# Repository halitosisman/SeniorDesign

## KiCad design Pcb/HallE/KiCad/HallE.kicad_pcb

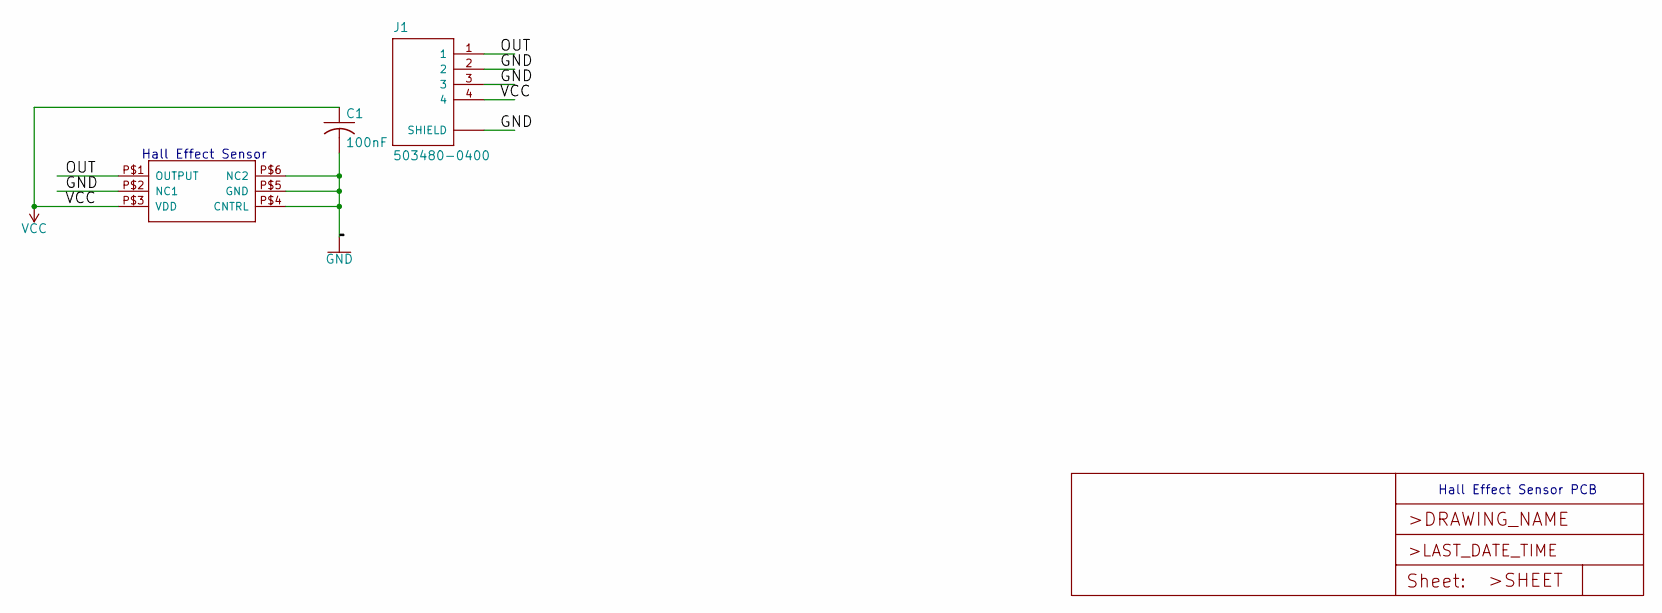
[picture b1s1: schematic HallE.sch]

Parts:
C1: 100nF; C0805
J1: 503480-0400; MOLEX_503480-0400
U$1: AH8503; UDFN-6

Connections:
/OUT: J1.1, U$1.P$1 (OUTPUT)
GND: C1.2, J1.2, J1.3, J1.S1 (SHIELD), J1.S2 (SHIELD), U$1.P$2 (NC1), U$1.P$4 (CNTRL), U$1.P$5 (GND), U$1.P$6 (NC2)
VCC: C1.1, J1.4, U$1.P$3 (VDD)

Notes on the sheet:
Hall Effect Sensor PCB
Hall Effect Sensor

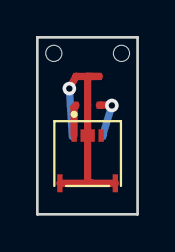
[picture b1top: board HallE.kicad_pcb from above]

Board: 2 copper layers, 5.6 x 9.8 mm, 5 parts (0 on the bottom side), 3 nets.

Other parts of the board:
@HOLE0, @HOLE1: (no value)

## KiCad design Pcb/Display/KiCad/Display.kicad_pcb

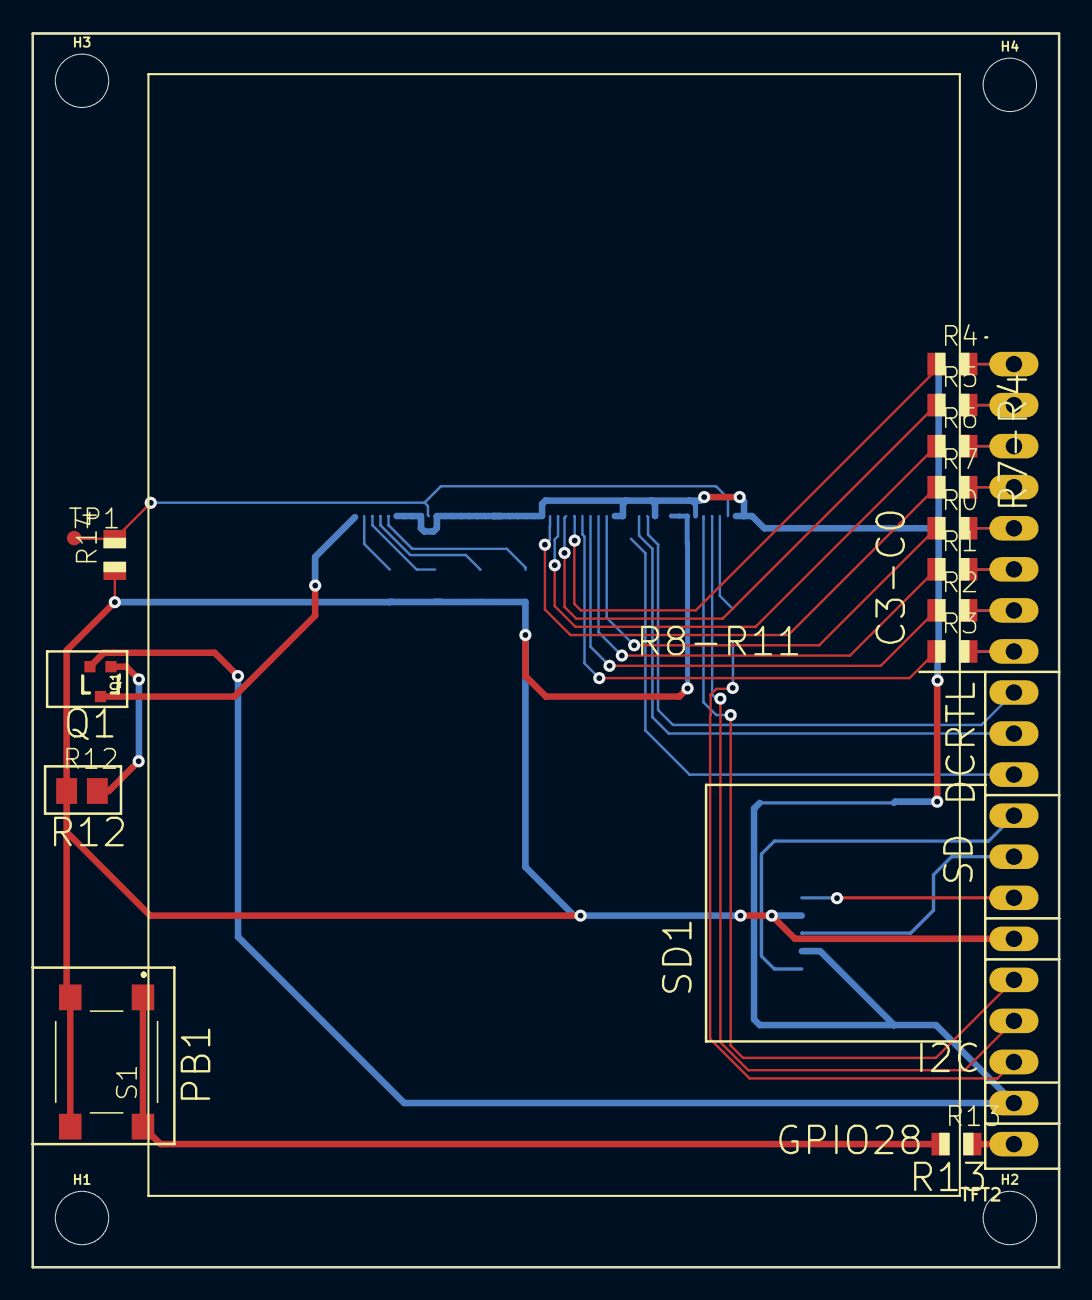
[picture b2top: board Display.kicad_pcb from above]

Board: 2 copper layers, 63.5 x 76.4 mm, 34 parts (0 on the bottom side), 37 nets.

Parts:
C0, C1, C2, C3, C4, C5, C6, C7: 10pF; C0805
H1, H2, H3, H4: STAND-OFF
J2: 47219-2001; MOLEX_47219-2001
JP4: Main PCB Header; 1X20
Q1: 310mA/60V/1.6Ω; SOT323
R0, R1, R2, R3, R4, R5, R6, R7, R8, R9, R10, R11, R14: 10; R0805
R12: 2.2k; M0805
R13: 100; R0805
R15: 1k; R0805
S1: B3FS-1000; B3FS1000
TFT2: DISP_LCD_CTP28_DATASHEET; TFT_CTP28
TP1: TPTP09R; TP09R

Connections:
/DB0: C0.1, JP4.16, R0.2
/DB1: C1.1, JP4.15, R1.2
/DB2: C2.1, JP4.14, R2.2
/DB3: C3.1, JP4.13, R3.2
/DB4: C4.1, JP4.20, R4.2
/DB5: C5.1, JP4.19, R5.2
/DB6: C6.1, JP4.18, R6.2
/DB7: C7.1, JP4.17, R7.2
/DCX: JP4.12, TFT2.37
/GPIO28: JP4.1, R13.2
/I2C_INT: JP4.3, R15.1
/I2C_SCL: JP4.5, TFT2.44
/I2C_SDA: JP4.4, TFT2.45
/R8: R8.2, TFT2.5
/R9: R9.2, TFT2.4
/R10: R10.2, TFT2.3
/R11: R11.2, TFT2.2
/R12: Q1.3, TFT2.1
/R13: R13.1, S1.1, S1.2
/RST: R14.2, TFT2.10, TFT2.47, TP1.TP
/SD_CLK: J2.5, JP4.8
/SD_CMD: J2.3, JP4.7
/SD_DAT0: J2.7, JP4.9
GND: C0.2, C1.2, C2.2, C3.2, C4.2, C5.2, C6.2, C7.2, J2.6, J2.G1, J2.G2, J2.G3, J2.G4, JP4.2, Q1.2, TFT2.6, TFT2.7, TFT2.8, TFT2.9, TFT2.11, TFT2.12, TFT2.13, TFT2.14, TFT2.15, TFT2.16, TFT2.17, TFT2.18, TFT2.19, TFT2.20, TFT2.21, TFT2.22, TFT2.23, TFT2.24, TFT2.33, TFT2.34, TFT2.38, TFT2.43, TFT2.48, TFT2.49, TFT2.50
unnamed: JP4.10, TFT2.36
unnamed: JP4.11, TFT2.35
unnamed: Q1.1, R12.2
unnamed: R0.1, TFT2.32
unnamed: R1.1, TFT2.31
unnamed: R2.1, TFT2.30
unnamed: R3.1, TFT2.29
unnamed: R4.1, TFT2.28
unnamed: R5.1, TFT2.27
unnamed: R6.1, TFT2.26
unnamed: R7.1, TFT2.25
unnamed: R15.2, TFT2.46
VCC: J2.4, JP4.6, R8.1, R9.1, R10.1, R11.1, R12.1, R14.1, S1.3, S1.4, TFT2.40, TFT2.41, TFT2.42

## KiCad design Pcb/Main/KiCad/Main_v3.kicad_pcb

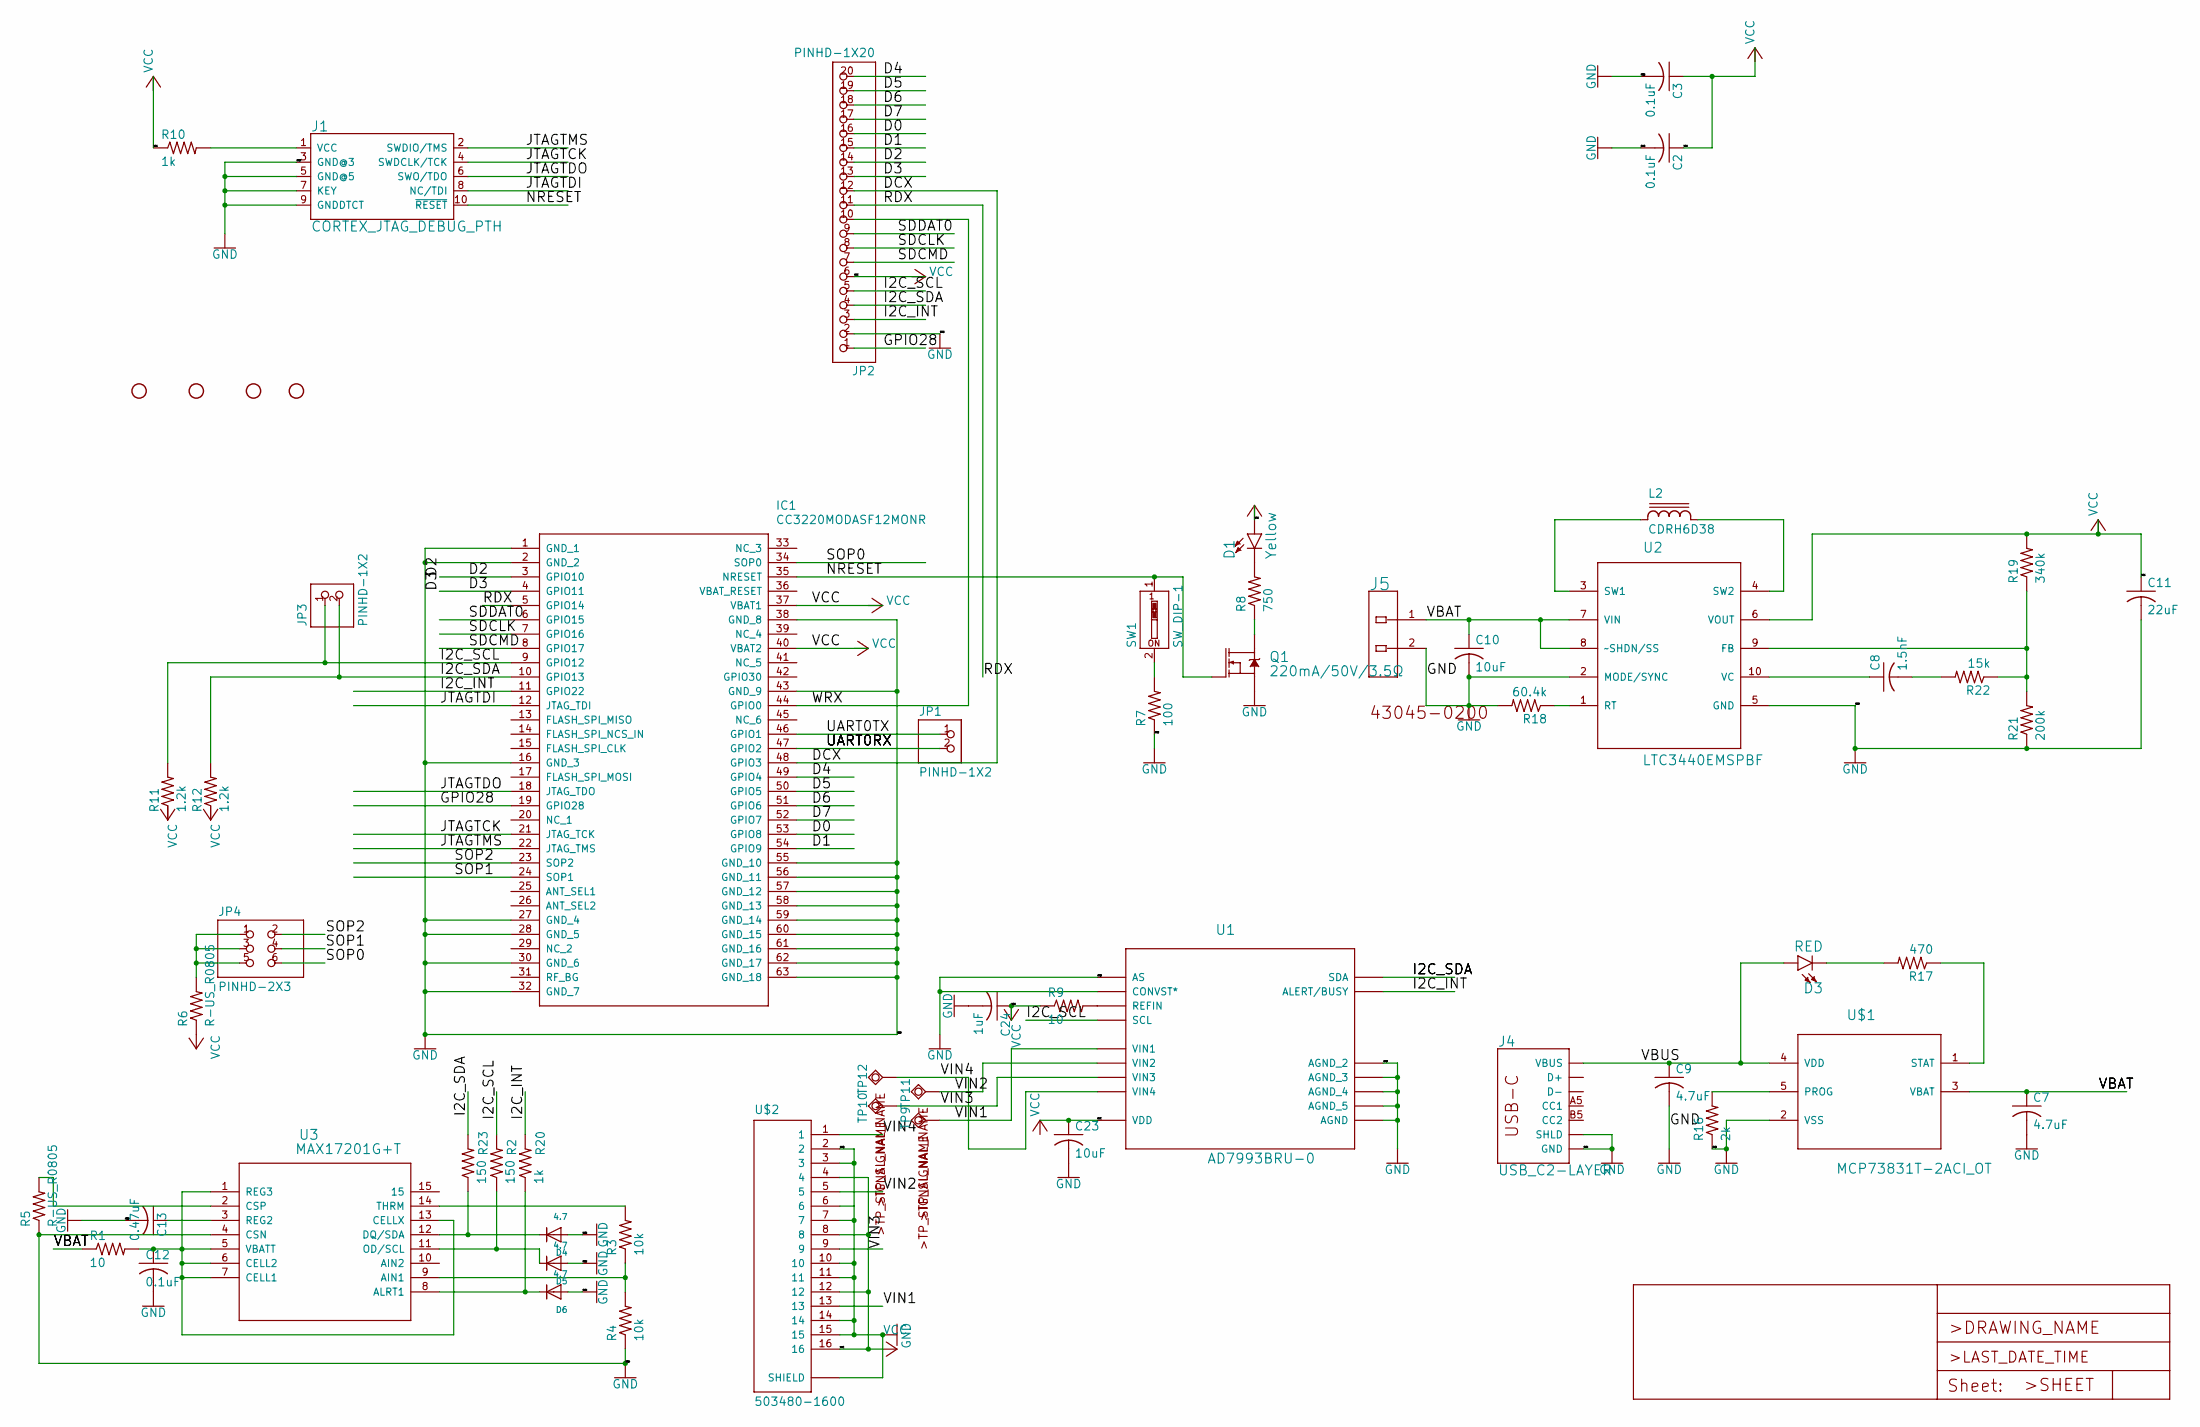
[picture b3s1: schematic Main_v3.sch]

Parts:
C2, C3, C12: 0.1uF; C0805
C7, C9: 4.7uF; C0805
C8: 1.5nF; C0805
C10, C23: 10uF; C0805
C11: 22uF; C1210
C13: 0.47uF; C0805
C24: 1uF; C0805
D1: Yellow; LED-0603
D3: RED; LED-0603
D4, D5, D6: 4.7; SOD-323F
H1, H2, H3, H4: STAND-OFF
IC1: CC3220MODASF12MONR; CC3220MODASM2MONR
J1: CORTEX_JTAG_DEBUG_PTH; 2X5-PTH-1.27MM
J4: USB_C2-LAYER; USB-C-16P
J5: MOLEX_43045-0200MOLEX_43045-0200_0_0; MOLEX_43045-0200_0
JP1, JP3: PINHD-1X2; 1X02
JP2: PINHD-1X20; 1X20
JP4: PINHD-2X3; 2X03
L2: CDRH6D38; CDRH6D
Q1: 220mA/50V/3.5Ω; SOT23-3
R1, R9: 10; R0805
R2, R23: 150; R0805
R3, R4: 10k; R0805
R5, R6: R-US_R0805; R0805
R7: 100; R0805
R8: 750; R0805
R10, R20: 1k; R0805
R11, R12: 1.2k; R0805
R16: 2k; R0805
R17: 470; R0805
R18: 60.4k; R0805
R19: 340k; R0805
R21: 200k; R0805
R22: 15k; R0805
SW1: SW_DIP-1; EDG-01
TP9, TP10, TP11, TP12: TPSQTP12R; TP12R
U1: AD7993BRU-0; SOP65P640X120-16N
U2: LTC3440EMSPBF; SOP50P490X110-10N
U3: MAX17201G+T; 21-0137I_T1433-1
U$1: MCP73831T-2ACI_OT; SOT95P280X145-5N
U$2: 503480-1600; MOLEX_503480-1600

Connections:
/D0: IC1.53 (GPIO8), JP2.16
/D1: IC1.54 (GPIO9), JP2.15
/D2: IC1.3 (GPIO10), JP2.14
/D3: IC1.4 (GPIO11), JP2.13
/D4: IC1.49 (GPIO4), JP2.20
/D5: IC1.50 (GPIO5), JP2.19
/D6: IC1.51 (GPIO6), JP2.18
/D7: IC1.52 (GPIO7), JP2.17
/DCX: IC1.48 (GPIO3), JP2.12
/GPIO28: IC1.19 (GPIO28), JP2.1
/I2C_INT: IC1.11 (GPIO22), JP2.3, R20.2, U1.13 (ALERT/BUSY)
/I2C_SCL: IC1.9 (GPIO12), JP2.5, JP3.1, R2.2, R11.2, U1.15 (SCL)
/I2C_SDA: IC1.10 (GPIO13), JP2.4, JP3.2, R12.2, R23.2, U1.14 (SDA)
/JTAGTCK: IC1.21 (JTAG_TCK), J1.4 (SWDCLK/TCK)
/JTAGTDI: IC1.12 (JTAG_TDI), J1.8 (NC/TDI)
/JTAGTDO: IC1.18 (JTAG_TDO), J1.6 (SWO/TDO)
/JTAGTMS: IC1.22 (JTAG_TMS), J1.2 (SWDIO/TMS)
/NRESET: IC1.35 (NRESET), J1.10 (~RESET), Q1.1 (G), SW1.1
/RDX: IC1.5 (GPIO14), JP2.11
/SDCLK: IC1.7 (GPIO16), JP2.8
/SDCMD: IC1.8 (GPIO17), JP2.7
/SDDAT0: IC1.6 (GPIO15), JP2.9
/SOP0: IC1.34 (SOP0), JP4.6
/SOP1: IC1.24 (SOP1), JP4.4
/SOP2: IC1.23 (SOP2), JP4.2
/UART0RX: IC1.47 (GPIO2), JP1.2
/UART0TX: IC1.46 (GPIO1), JP1.1
/VBAT: C7.1, C10.1, J5.1, R1.1, U2.7 (VIN), U2.8 (~~SHDN/SS), U$1.3 (VBAT)
/VBUS: C9.1, D3.A, J4.VBUS1 (VBUS), J4.VBUS2 (VBUS), U$1.4 (VDD)
/VIN1: TP9.TP, U1.7 (VIN1), U$2.13
/VIN2: TP11.TP, U1.10 (VIN2), U$2.5
/VIN3: TP10.TP, U1.8 (VIN3), U$2.9
/VIN4: TP12.TP, U1.9 (VIN4), U$2.1
/WRX: IC1.44 (GPIO0), JP2.10
unnamed: C8.1, U2.10 (VC)
unnamed: C8.2, R22.2
unnamed: C12.1, R1.2, U3.1 (REG3), U3.5 (VBATT), U3.6 (CELL2), U3.7 (CELL1), U3.13 (CELLX)
unnamed: C13.1, U3.3 (REG2)
unnamed: D1.C, R8.2
unnamed: D3.C, R17.2
unnamed: D4.C, R23.1, U3.12 (DQ/SDA)
unnamed: D5.C, R2.1, U3.11 (OD/SCL)
unnamed: D6.C, R20.1, U3.8 (ALRT1)
unnamed: J1.1 (VCC), R10.2
unnamed: J4.A6 (D+), J4.B6 (D+)
unnamed: J4.A7 (D-), J4.B7 (D-)
unnamed: JP4.1, JP4.3, JP4.5, R6.2
unnamed: L2.1, U2.3 (SW1)
unnamed: L2.2, U2.4 (SW2)
unnamed: Q1.3 (D), R8.1
unnamed: R3.1, R4.2, U3.9 (AIN1)
unnamed: R3.2, U3.14 (THRM)
unnamed: R5.2, U3.2 (CSP)
unnamed: R7.2, SW1.2
unnamed: R9.2, U1.6 (REFIN)
unnamed: R16.2, U$1.5 (PROG)
unnamed: R17.1, U$1.1 (STAT)
unnamed: R18.1, U2.1 (RT)
unnamed: R19.1, R21.2, R22.1, U2.9 (FB)

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
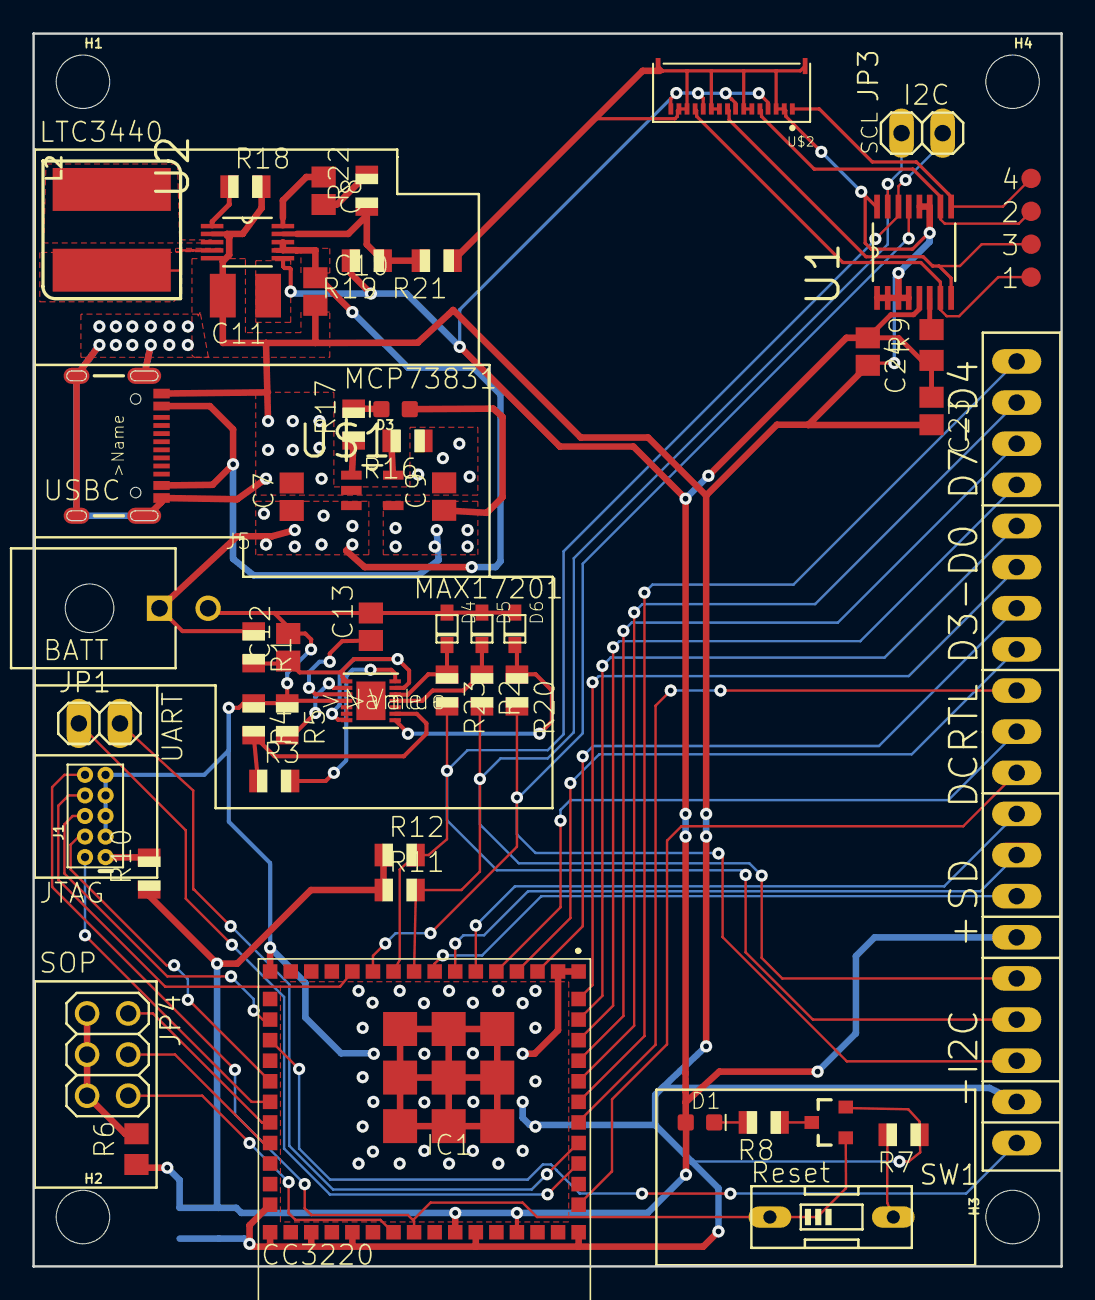
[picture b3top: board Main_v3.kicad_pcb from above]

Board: 2 copper layers, 63.5 x 76.1 mm, 60 parts (0 on the bottom side), 61 nets.

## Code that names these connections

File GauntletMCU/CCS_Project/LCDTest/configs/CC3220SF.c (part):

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PowerCC32XX_ParkInfo parkInfo[] = {
/*          PIN                    PARK STATE              PIN ALIAS (FUNCTION)
     -----------------  ------------------------------     -------------------- */
    {PowerCC32XX_PIN01, PowerCC32XX_WEAK_PULL_DOWN_STD}, /* GPIO10              */
    {PowerCC32XX_PIN02, PowerCC32XX_WEAK_PULL_DOWN_STD}, /* GPIO11              */
    {PowerCC32XX_PIN03, PowerCC32XX_WEAK_PULL_DOWN_STD}, /* GPIO12              */
    {PowerCC32XX_PIN04, PowerCC32XX_WEAK_PULL_DOWN_STD}, /* GPIO13              */
    {PowerCC32XX_PIN05, PowerCC32XX_WEAK_PULL_DOWN_STD}, /* GPIO14              */
    {PowerCC32XX_PIN06, PowerCC32XX_WEAK_PULL_DOWN_STD}, /* GPIO15              */
    {PowerCC32XX_PIN07, PowerCC32XX_WEAK_PULL_DOWN_STD}, /* GPIO16              */
    {PowerCC32XX_PIN08, PowerCC32XX_WEAK_PULL_DOWN_STD}, /* GPIO17              */
    {PowerCC32XX_PIN13, PowerCC32XX_WEAK_PULL_DOWN_STD}, /* FLASH_SPI_DIN       */
    {PowerCC32XX_PIN15, PowerCC32XX_WEAK_PULL_DOWN_STD}, /* GPIO22              */
    {PowerCC32XX_PIN16, PowerCC32XX_WEAK_PULL_DOWN_STD}, /* TDI (JTAG DEBUG)    */
    {PowerCC32XX_PIN17, PowerCC32XX_WEAK_PULL_DOWN_STD}, /* TDO (JTAG DEBUG)    */
    {PowerCC32XX_PIN19, PowerCC32XX_WEAK_PULL_DOWN_STD}, /* TCK (JTAG DEBUG)    */
    {PowerCC32XX_PIN20, PowerCC32XX_WEAK_PULL_DOWN_STD}, /* TMS (JTAG DEBUG)    */
    {PowerCC32XX_PIN18, PowerCC32XX_WEAK_PULL_DOWN_STD}, /* GPIO28              */
    {PowerCC32XX_PIN21, PowerCC32XX_WEAK_PULL_DOWN_STD}, /* SOP2                */
    {PowerCC32XX_PIN29, PowerCC32XX_WEAK_PULL_DOWN_STD}, /* ANTSEL1             */
    {PowerCC32XX_PIN30, PowerCC32XX_WEAK_PULL_DOWN_STD}, /* ANTSEL2             */
    {PowerCC32XX_PIN45, PowerCC32XX_WEAK_PULL_DOWN_STD}, /* DCDC_ANA2_SW_P      */
    {PowerCC32XX_PIN50, PowerCC32XX_WEAK_PULL_DOWN_STD}, /* GPIO0               */
    {PowerCC32XX_PIN52, PowerCC32XX_WEAK_PULL_DOWN_STD}, /* RTC_XTAL_N          */
    {PowerCC32XX_PIN53, PowerCC32XX_WEAK_PULL_DOWN_STD}, /* GPIO30              */
    {PowerCC32XX_PIN55, PowerCC32XX_WEAK_PULL_UP_STD},   /* GPIO1 (XDS_UART_RX) */
    {PowerCC32XX_PIN57, PowerCC32XX_WEAK_PULL_UP_STD},   /* GPIO2 (XDS_UART_TX) */
    {PowerCC32XX_PIN58, PowerCC32XX_WEAK_PULL_DOWN_STD}, /* GPIO3               */
    {PowerCC32XX_PIN59, PowerCC32XX_WEAK_PULL_DOWN_STD}, /* GPIO4               */
    {PowerCC32XX_PIN60, PowerCC32XX_WEAK_PULL_DOWN_STD}, /* GPIO5               */
    {PowerCC32XX_PIN61, PowerCC32XX_WEAK_PULL_DOWN_STD}, /* GPIO6               */
    {PowerCC32XX_PIN62, PowerCC32XX_WEAK_PULL_DOWN_STD}, /* GPIO7               */
    {PowerCC32XX_PIN63, PowerCC32XX_WEAK_PULL_DOWN_STD}, /* GPIO8               */
    {PowerCC32XX_PIN64, PowerCC32XX_WEAK_PULL_DOWN_STD}, /* GPIO9               */
};

/*
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
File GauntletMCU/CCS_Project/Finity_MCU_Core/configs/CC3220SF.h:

/*
 * Copyright (c) 2016-2018, Texas Instruments Incorporated
 * All rights reserved.
 *
 * Redistribution and use in source and binary forms, with or without
 * modification, are permitted provided that the following conditions
 * are met:
 *
 * *  Redistributions of source code must retain the above copyright
 *    notice, this list of conditions and the following disclaimer.
 *
 * *  Redistributions in binary form must reproduce the above copyright
 *    notice, this list of conditions and the following disclaimer in the
 *    documentation and/or other materials provided with the distribution.
 *
 * *  Neither the name of Texas Instruments Incorporated nor the names of
 *    its contributors may be used to endorse or promote products derived
 *    from this software without specific prior written permission.
 *
 * THIS SOFTWARE IS PROVIDED BY THE COPYRIGHT HOLDERS AND CONTRIBUTORS "AS IS"
 * AND ANY EXPRESS OR IMPLIED WARRANTIES, INCLUDING, BUT NOT LIMITED TO,
 * THE IMPLIED WARRANTIES OF MERCHANTABILITY AND FITNESS FOR A PARTICULAR
 * PURPOSE ARE DISCLAIMED. IN NO EVENT SHALL THE COPYRIGHT OWNER OR
 * CONTRIBUTORS BE LIABLE FOR ANY DIRECT, INDIRECT, INCIDENTAL, SPECIAL,
 * EXEMPLARY, OR CONSEQUENTIAL DAMAGES (INCLUDING, BUT NOT LIMITED TO,
 * PROCUREMENT OF SUBSTITUTE GOODS OR SERVICES; LOSS OF USE, DATA, OR PROFITS;
 * OR BUSINESS INTERRUPTION) HOWEVER CAUSED AND ON ANY THEORY OF LIABILITY,
 * WHETHER IN CONTRACT, STRICT LIABILITY, OR TORT (INCLUDING NEGLIGENCE OR
 * OTHERWISE) ARISING IN ANY WAY OUT OF THE USE OF THIS SOFTWARE,
 * EVEN IF ADVISED OF THE POSSIBILITY OF SUCH DAMAGE.
 */
/** ============================================================================
 *  @file       C3220SF_LAUNCHXL.h
 *
 *  @brief      CC3220 Board Specific APIs
 *
 *  The CC3220SF_LAUNCHXL header file should be included in an application as
 *  follows:
 *  @code
 *  #include <CC3220SF_LAUNCHXL.h>
 *  @endcode
 *
 *  ============================================================================
 */
#ifndef __CC3220SF_LAUNCHXL_H
#define __CC3220SF_LAUNCHXL_H


#include "stdint.h"
#include <ti/drivers/I2C.h>

/* Common interface includes                                                 */
#include "tasks/net_task/network_if.h"
#include "util/uart_term.h"


#ifdef __cplusplus
extern "C" {
#endif

UART_Handle uart_debug;

typedef enum CC3220SF_LAUNCHXL_SPIName {
    CC3220SF_LAUNCHXL_SPI0 = 0,

    CC3220SF_LAUNCHXL_SPICOUNT
} CC3220SF_LAUNCHXL_SPIName;

typedef enum {
    GPIO_RDX = 0,
    GPIO_WRX,
    GPIO_DCX,
    GPIO_D7,
    GPIO_D6,
    GPIO_D5,
    GPIO_D4,
    GPIO_D3,
    GPIO_D2,
    GPIO_D1,
    GPIO_D0,
    GPIO_I2C_Int,
    GPIO_Pin_Count
} GPIO_Settings;

void i2c_int_callback(uint_least8_t index);

extern void CC3220SF_LAUNCHXL_initGeneral(void);

#ifdef __cplusplus
}
#endif

#endif /* __CC3220SF_LAUNCHXL_H */

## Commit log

2020-03-09 Added Pcb design files
2020-04-03 Updated PCB files and ported some of the graphics functions. The graphics changes are not tested yet.
2020-04-03 First draft of Graphics Port. Also moved all peripheral initializations to a single function where they probably belong.
2020-04-12 Everything works again.
2020-04-13 Deleted example projects. Base TI graphics functionality implemented.
2020-04-18 Added LCD functionality into core project and started work on GUI layer.
2020-04-19 2/3 GUI prototypes.
2020-04-20 Began I2C thread work
2020-04-20 GUI stuff working and first draft of ADC drivers.
2020-04-21 First contact between I2C and ADC.
2020-04-21 Added a picture of the circuitboard schematic
2020-04-22 ADC over I2C functionality implemented.
2020-04-22 Added some things I forgot to handle earlier.
2020-04-22 Ongoing work on i2c and gui task integration.
2020-04-23 Project compiles now. Still need to integrate MQTT stuff.
2020-04-24 Minor indenting changes.
2020-04-24 Continued work on state machine.
2020-04-25 More integration stuff. It compiles without warnings.
2020-04-25 First Draft of integrated code. A remaining GUI element still needs to be implemented.
2020-04-26 Fixed I2C_open fault, made the taskhandles get properly referenced from within threads. God I wish TI would fix their driver bugs.
2020-04-27 Got I2C alerts working.
2020-04-27 I2C integration finished. Networking integration started.
2020-04-28 Pretty sure the cause of bugs is TI's signature undocumented POSIX behaviors.
2020-04-28 Hopefully everything works fine in POSIX form now.
2020-04-29 It actually works
2020-04-29 Enhanced GUI v1 added.
2020-04-29 Added some of Daniel's stuff and cleaned up a load of other unused stuff.
2020-04-29 Ongoing work on removing hardcoded GUI values and allowing has-a relationships between GUI windows.
2020-04-29 More GUI work.
2020-04-30 First Draft of the fancy spanking GUI.
2020-04-30 Most bugs ironed out. GUI is functional.
2020-04-30 I added a space
2020-05-04 Added some stuff to the 3d mockup file and a bunch of comments to the main project.
2020-05-04 Finished Documenting Peter's stuff.
2020-05-04 Added Daniel's comments.
2020-05-04 Some cleanup.

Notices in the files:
GauntletMCU/CCS_Project/LCDTest/configs/CC3220SF.c:
Copyright (c) 2016-2019, Texas Instruments Incorporated
All rights reserved.
parts and their libraries:
SparkFun-PowerSymbols: Licensing: Creative Commons ShareAlike 4.0 International - https://creativecommons.org/licenses/by-sa/4.0
AD7993BRU-0: COPYRIGHT: Copyright (C) 2018 Accelerated Designs. All rights reserved
